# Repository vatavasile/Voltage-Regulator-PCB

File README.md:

# USB-C Voltage Regulator PCB

## Overview
This project is a custom PCB designed as part of a university exercise. The goal was to design and route a functional USB-C (USB 2.0) interface using KiCad while respecting PCB design rules and manufacturing constraints.

---

## Objectives
- Design a USB-C connector interface  
- Implement correct CC configuration for device mode  
- Route USB data lines (D+ / D−)  
- Handle power distribution (VBUS & GND)  
- Ensure manufacturability using Design Rule Checks (DRC)  

---

## Project Preview

### PCB Layout

### Schematic

---

## Notes
This project was completed as part of a university exercise to develop practical skills in PCB design, routing, and hardware engineering fundamentals.

---

## Author
Vasile Vataman  
Electrical & Electronics Engineering Student

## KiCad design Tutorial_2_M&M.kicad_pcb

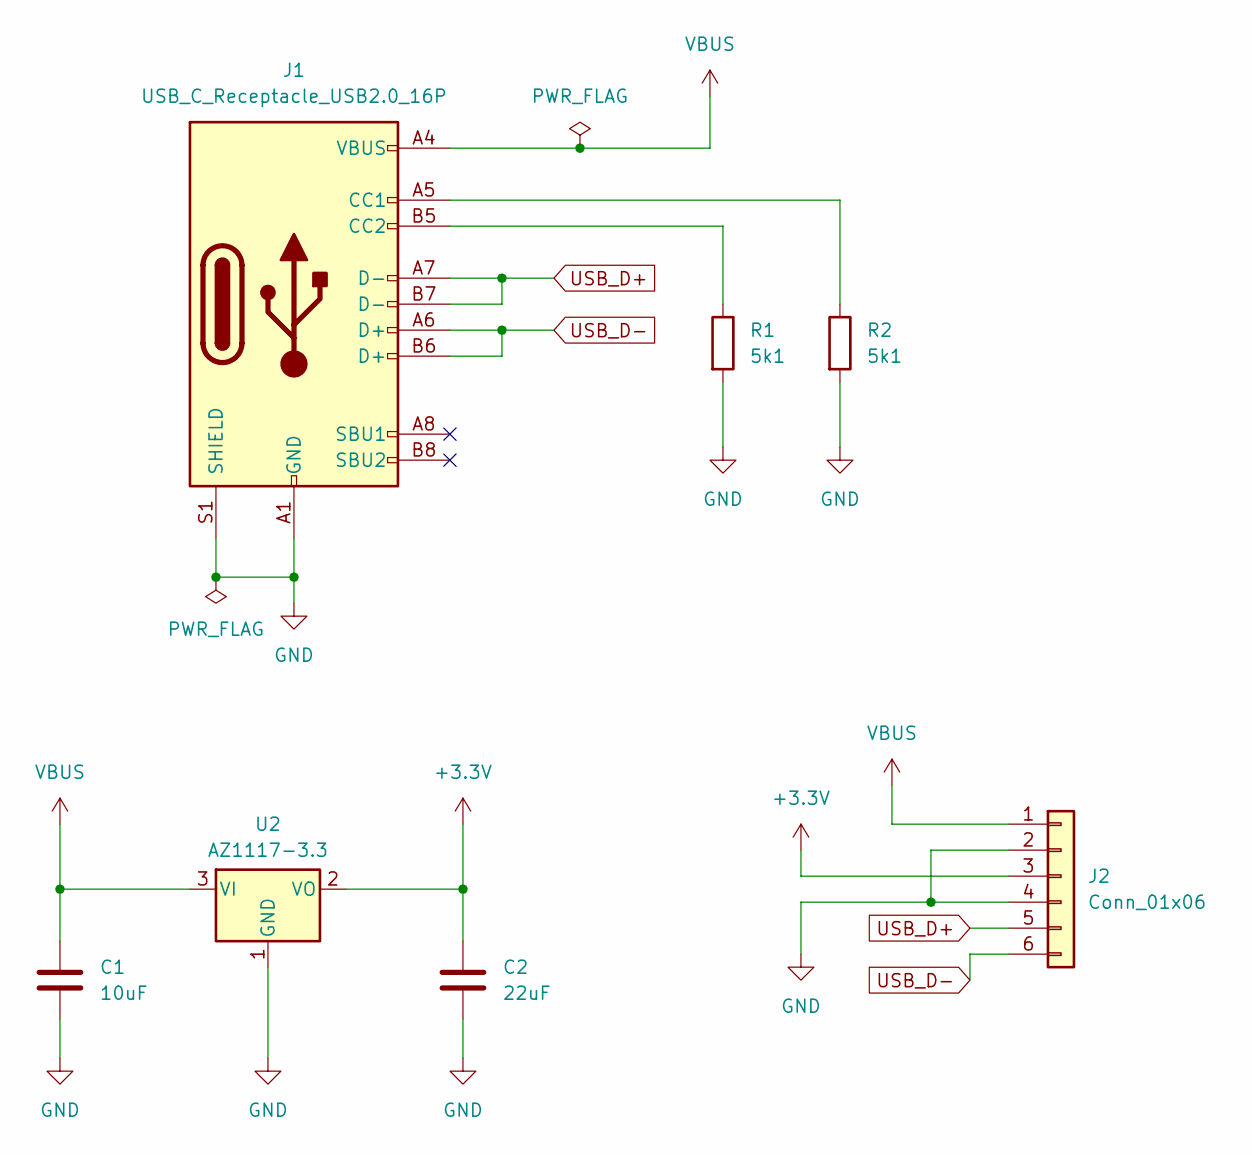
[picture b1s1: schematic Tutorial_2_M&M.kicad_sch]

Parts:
C1: 10uF; C_0603_1608Metric
C2: 22uF; C_0603_1608Metric
J1: USB_C_Receptacle_USB2.0_16P; USB_C_Receptacle_GCT_USB4105-xx-A_16P_TopMnt_Horizontal
J2: Conn_01x06; PinHeader_1x06_P2.54mm_Vertical_SMD_Pin1Left
R1, R2: 5k1; R_0603_1608Metric
U2: AZ1117-3.3; SOT-223-3_TabPin2

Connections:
+3.3V: C2.1, J2.3, U2.2 (VO)
GND: C1.2, C2.2, J1.A1 (GND), J1.A12 (GND), J1.B1 (GND), J1.B12 (GND), J1.S1 (SHIELD), J2.2, J2.4, R1.2, R2.2, U2.1 (GND)
unnamed: J1.A5 (CC1), R2.1
unnamed: J1.B5 (CC2), R1.1
USB_D+: J1.A7 (D-), J1.B7 (D-), J2.5
USB_D-: J1.A6 (D+), J1.B6 (D+), J2.6
VBUS: C1.1, J1.A4 (VBUS), J1.A9 (VBUS), J1.B4 (VBUS), J1.B9 (VBUS), J2.1, U2.3 (VI)

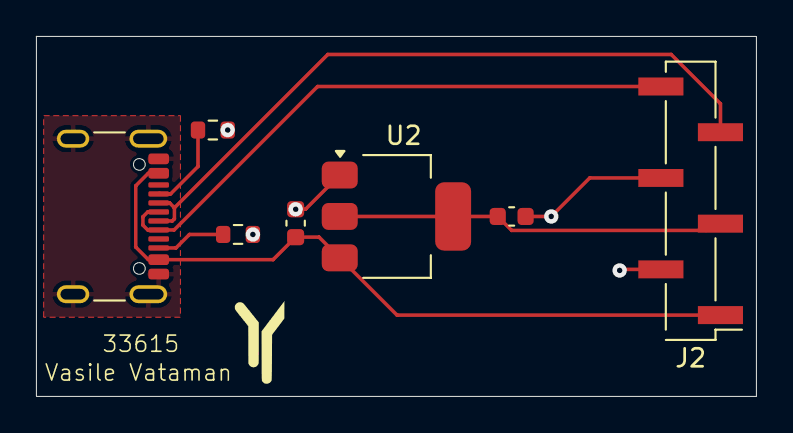
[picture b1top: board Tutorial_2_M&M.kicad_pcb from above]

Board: 2 copper layers, 40.0 x 20.0 mm, 7 parts (0 on the bottom side), 7 nets.

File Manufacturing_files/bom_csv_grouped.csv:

"Reference","Qty","Value","DNP","Exclude from BOM","Exclude from Board","Footprint","Datasheet"
"C1","1","10uF","","","","Capacitor_SMD:C_0603_1608Metric","~"
"C2","1","22uF","","","","Capacitor_SMD:C_0603_1608Metric","~"
"J1","1","USB_C_Receptacle_USB2.0_16P","","","","Connector_USB:USB_C_Receptacle_GCT_USB4105-xx-A_16P_TopMnt_Horizontal","https://www.usb.org/sites/default/files/documents/usb_type-c.zip"
"J2","1","Conn_01x06","","","","Connector_PinHeader_2.54mm:PinHeader_1x06_P2.54mm_Vertical_SMD_Pin1Left","~"
"R1,R2","2","5k1","","","","Resistor_SMD:R_0603_1608Metric","~"
"U2","1","AZ1117-3.3","","","","Package_TO_SOT_SMD:SOT-223-3_TabPin2","https://www.diodes.com/assets/Datasheets/AZ1117.pdf"

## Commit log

2026-04-29 initial commit of the project
2026-04-29 PCB layout completed
2026-04-29 Add README.md for USB-C Voltage Regulator project
    Added project overview, objectives, tools used, features, and project preview images.
2026-04-29 Update README.md~
2026-04-29 Pictures added
2026-04-29 readme fixed
2026-04-29 Refactor README.md for clarity and conciseness
    Removed redundant sections and updated formatting.
2026-04-29 Fix formatting and image links in README.md
    Corrected image links and formatting issues in the README.
2026-05-02 GND Zone added on F.Cu & Gerber Files created
2026-05-02 layout image updated
